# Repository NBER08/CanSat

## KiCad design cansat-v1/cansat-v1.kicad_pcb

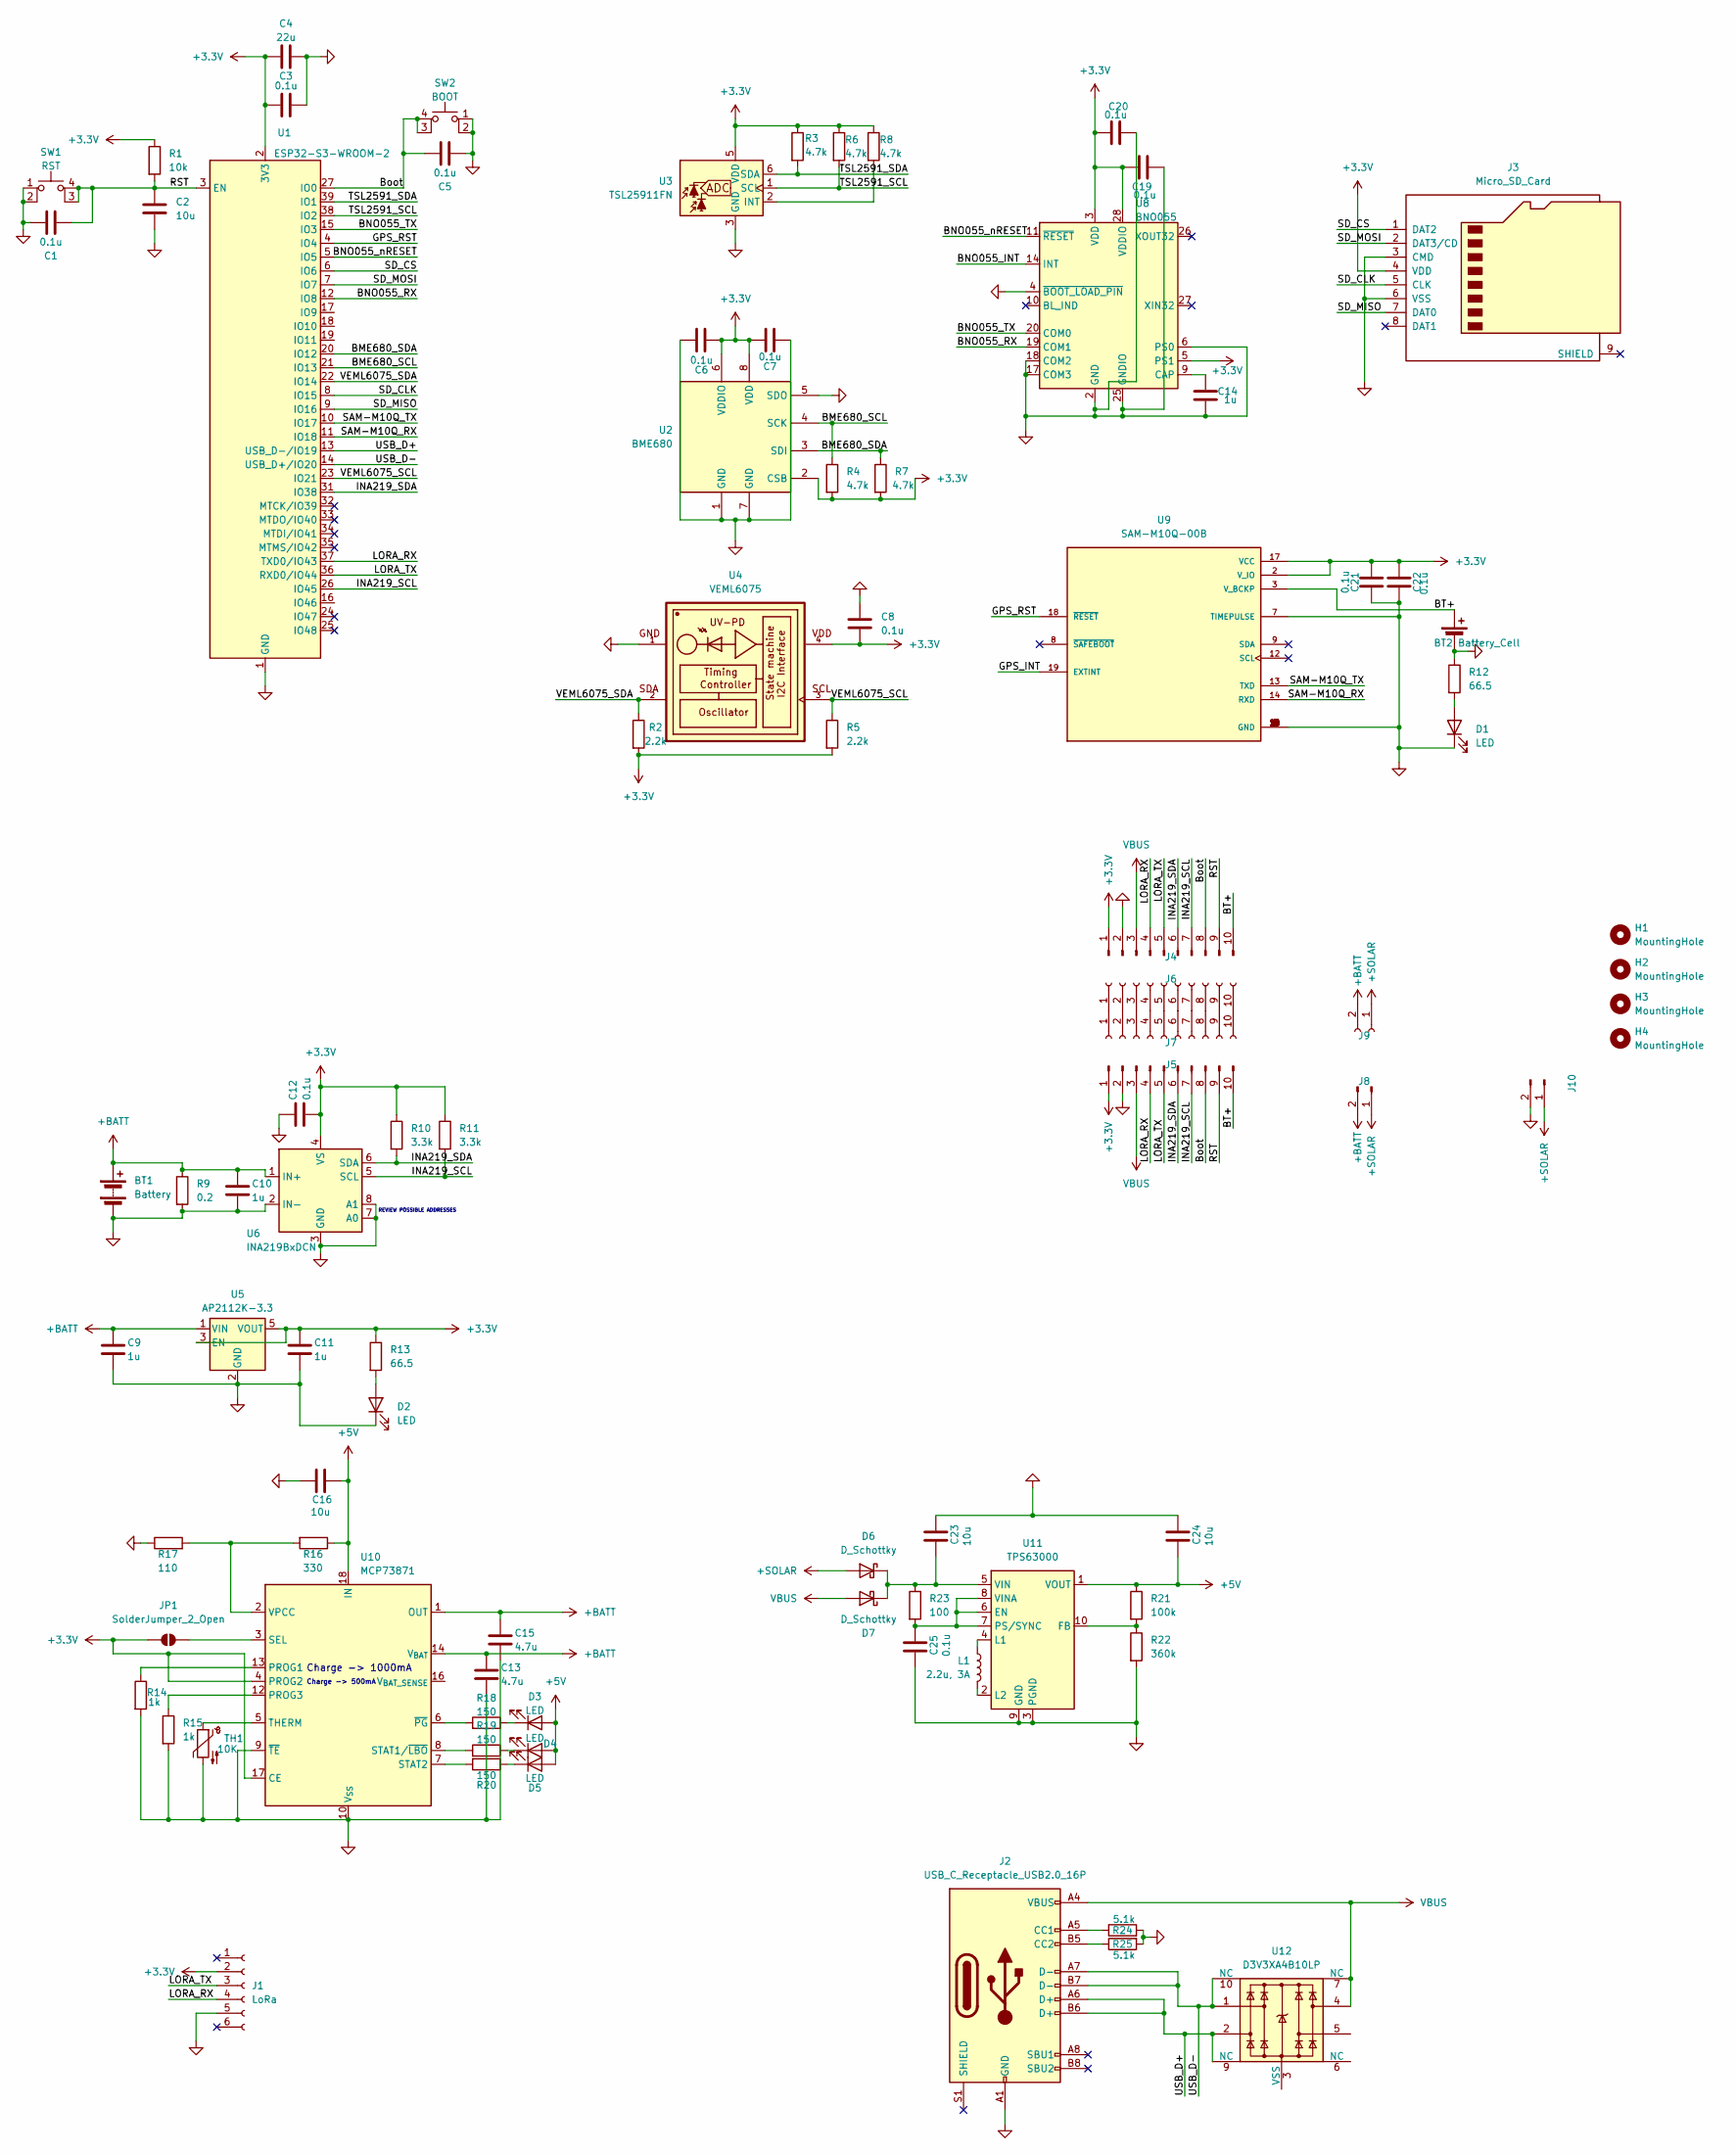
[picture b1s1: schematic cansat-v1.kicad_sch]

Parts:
BT1: Battery; AMASS_XT60-F_1x02_P7.20mm_Vertical
BT2: Battery_Cell; BatteryHolder_Keystone_3034_1x20mm
C1, C3, C5, C6, C7, C8, C12, C19, C20, C21, C22, C25: 0.1u; C_0603_1608Metric
C2, C16, C23, C24: 10u; C_0603_1608Metric
C4: 22u; C_0603_1608Metric
C9, C10, C11, C14: 1u; C_0603_1608Metric
C13, C15: 4.7u; C_0603_1608Metric
D1, D2, D3, D4, D5: LED; LED_1206_3216Metric_Pad1.42x1.75mm_HandSolder
D6, D7: D_Schottky; D_0603_1608Metric
H1, H2, H3, H4: MountingHole; MountingHole_3.2mm_M3
J1: LoRa; PinSocket_1x06_P2.54mm_Horizontal
J2: USB_C_Receptacle_USB2.0_16P; USB_C_Receptacle_G-Switch_GT-USB-7010ASV
J3: Micro_SD_Card; microSD_HC_Wuerth_693072010801
J4, J5: Conn_01x08_Pin; PinHeader_1x10_P2.54mm_Horizontal
J6, J7: Conn_01x08_Socket; PinSocket_1x10_P2.54mm_Vertical
J8: Conn_01x02_Pin; PinHeader_1x02_P2.54mm_Horizontal
J9: Conn_01x02_Socket; PinSocket_1x02_P2.54mm_Vertical
J10: Conn_01x02_Pin; JST_XH_B2B-XH-A_1x02_P2.50mm_Vertical
JP1: SolderJumper_2_Open; SolderJumper-2_P1.3mm_Open_TrianglePad1.0x1.5mm
L1: 2.2u, 3A; L_0603_1608Metric
R1: 10k; R_0603_1608Metric
R2, R5: 2.2k; R_0603_1608Metric
R3, R4, R6, R7, R8: 4.7k; R_0603_1608Metric
R9: 0.2; R_0603_1608Metric
R10, R11: 3.3k; R_0603_1608Metric
R12, R13: 66.5; R_1206_3216Metric
R14, R15: 1k; R_1206_3216Metric
R16: 330; R_1206_3216Metric
R17: 110; R_1206_3216Metric
R18, R19, R20: 150; R_1206_3216Metric
R21: 100k; R_1206_3216Metric
R22: 360k; R_1206_3216Metric
R23: 100; R_1206_3216Metric
R24, R25: 5.1k; R_1206_3216Metric
SW1: RST; SW_MEC_5GSH9
SW2: BOOT; SW_MEC_5GSH9
TH1: 10K; R_0603_1608Metric
U1: ESP32-S3-WROOM-2
U2: BME680; Bosch_LGA-8_3x3mm_P0.8mm_ClockwisePinNumbering
U3: TSL25911FN; AMS_TSL25911FN
U4: VEML6075; VISHAY_VEML6075_1.25X2X1
U5: AP2112K-3.3; SOT-23-5
U6: INA219BxDCN; SOT-23-8
U8: BNO055; LGA-28_5.2x3.8mm_P0.5mm
U9: SAM-M10Q-00B; XCVR_SAM-M10Q-00B; PARTREV R03
U10: MCP73871; QFN-20-1EP_4x4mm_P0.5mm_EP2.5x2.5mm
U11: TPS63000; Texas_DRC0010J_ThermalVias
U12: D3V3XA4B10LP; Diodes_UDFN-10_1.0x2.5mm_P0.5mm

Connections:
+3.3V: C3.1, C4.1, C6.1, C7.2, C8.2, C11.1, C12.2, C19.2, C20.2, C21.1, C22.1, J1.2, J3.4 (VDD), J4.1, J5.1, JP1.1 (A), R1.1, R2.2, R3.1, R4.2, R5.2, R6.1, R7.2, R8.1, R10.1, R11.1, R13.1, U1.2 (3V3), U2.2 (CSB), U2.6 (VDDIO), U2.8 (VDD), U3.5 (VDD), U4.4, U5.3 (EN), U5.5 (VOUT), U6.4 (VS), U8.3 (VDD), U8.5 (PS1), U8.28 (VDDIO), U9.2 (V_IO), U9.17 (VCC), U10.4 (PROG2), U10.17 (CE)
+5V: C16.1, C24.2, D3.2 (A), D4.2 (A), D5.2 (A), R16.1, R21.1, U10.18 (IN), U10.19 (IN), U11.1 (VOUT)
+BATT: BT1.1 (+), C9.1, C10.1, C13.1, C15.1, J8.2, J9.2, R9.1, U5.1 (VIN), U6.1 (IN+), U10.1 (OUT), U10.14 (V_{BAT}), U10.15 (V_{BAT}), U10.20 (OUT); also elsewhere on the board
+SOLAR: D6.2 (A), J8.1, J9.1, J10.1; also elsewhere on the board
/BME680_SCL: R4.1, U1.21 (IO13), U2.4 (SCK)
/BME680_SDA: R7.1, U1.20 (IO12), U2.3 (SDI)
/BNO055_INT: U8.14 (INT)
/BNO055_RX: U1.12 (IO8), U8.19 (COM1)
/BNO055_TX: U1.15 (IO3), U8.20 (COM0)
/BNO055_nRESET: U1.5 (IO5), U8.11 (~RESET)
/BT+: BT2.1 (+), J4.10, J5.10, U9.3 (V_BCKP)
/Boot: C5.2, J4.8, J5.8, SW2.3 (K), SW2.4 (A), U1.27 (IO0)
/GPS_INT: U9.19 (EXTINT)
/GPS_RST: U1.4 (IO4), U9.18 (~RESET)
/INA219_SCL: J4.7, J5.7, R11.2, U1.26 (IO45), U6.5 (SCL)
/INA219_SDA: J4.6, J5.6, R10.2, U1.31 (IO38), U6.6 (SDA)
/LORA_RX: J1.4, J4.4, J5.4, U1.37 (TXD0/IO43)
/LORA_TX: J1.3, J4.5, J5.5, U1.36 (RXD0/IO44)
/RST: C1.2, C2.1, J4.9, J5.9, R1.2, SW1.3 (K), SW1.4 (A), U1.3 (EN)
/SAM-M10Q_RX: U1.11 (IO18), U9.14 (RXD)
/SAM-M10Q_TX: U1.10 (IO17), U9.13 (TXD)
/SD_CLK: J3.5 (CLK), U1.8 (IO15)
/SD_CS: J3.1 (DAT2), U1.6 (IO6)
/SD_MISO: J3.7 (DAT0), U1.9 (IO16)
/SD_MOSI: J3.2 (DAT3/CD), U1.7 (IO7)
/TSL2591_SCL: R6.2, U1.38 (IO2), U3.1 (SCL)
/TSL2591_SDA: R3.2, U1.39 (IO1), U3.6 (SDA)
/USB_D+: J2.A6 (D+), J2.B6 (D+), U1.13 (USB_D-/IO19), U12.2, U12.9 (NC)
/USB_D-: J2.A7 (D-), J2.B7 (D-), U1.14 (USB_D+/IO20), U12.1, U12.10 (NC)
/VEML6075_SCL: R5.1, U1.23 (IO21), U4.3
/VEML6075_SDA: R2.1, U1.22 (IO14), U4.2
GND: BT1.2 (-), BT2.2 (-), C1.1, C2.2, C3.2, C4.2, C5.1, C6.2, C7.1, C8.1, C9.2, C10.2, C11.2, C12.1, C13.2, C14.2, C15.2, C16.2, C19.1, C20.1, C21.2, C22.2, C23.1, C24.1, C25.2, D1.1 (K), D2.1 (K), J1.5, J2.A1 (GND), J2.A12 (GND), J2.B1 (GND), J2.B12 (GND), J3.3 (CMD), J3.6 (VSS), J4.2, J5.2, J10.2, R9.2, R12.1, R14.2, R15.2, R17.1, R22.2, R24.2, R25.2, SW1.1, SW1.2, SW2.1, SW2.2, TH1.2, U1.1 (GND), U1.40 (GND), U1.41 (GND), U2.1 (GND), U2.5 (SDO), U2.7 (GND), U3.3 (GND), U4.1, U5.2 (GND), U6.2 (IN-), U6.3 (GND), U6.7 (A0), U6.8 (A1), U8.2 (GND), U8.4 (~BOOT_LOAD_PIN), U8.6 (PS0), U8.17 (COM3), U8.18 (COM2), U8.25 (GNDIO), U9.1 (GND), U9.4 (GND), U9.5 (GND), U9.6 (GND), U9.7 (TIMEPULSE), U9.10 (GND), U9.11 (GND), U9.15 (GND), U9.16 (GND), U9.20 (GND), U10.9 (~TE), U10.10 (V_{SS}), U10.11 (V_{SS}), U10.21 (V_{SS}), U11.3 (PGND), U11.9 (GND), U11.11 (PGND)
unnamed: D1.2 (A), R12.2
unnamed: D2.2 (A), R13.2
unnamed: D3.1 (K), R18.1
unnamed: D4.1 (K), R19.1
unnamed: D5.1 (K), R20.1
unnamed: C23.2, D6.1 (K), D7.1 (K), R23.1, U11.5 (VIN)
unnamed: J2.A5 (CC1), R24.1
unnamed: J2.B5 (CC2), R25.1
unnamed: J6.1, J7.1
unnamed: J6.2, J7.2
unnamed: J6.3, J7.3
unnamed: J6.4, J7.4
unnamed: J6.5, J7.5
unnamed: J6.6, J7.6
unnamed: J6.7, J7.7
unnamed: J6.8, J7.8
unnamed: J6.9, J7.9
unnamed: J6.10, J7.10
unnamed: JP1.2 (B), U10.3 (SEL)
unnamed: R8.2, U3.2 (INT)
unnamed: C14.1, U8.9 (CAP)
unnamed: R14.1, U10.13 (PROG1)
unnamed: R15.1, U10.12 (PROG3)
unnamed: R19.2, U10.8 (STAT1/~LBO)
unnamed: R20.2, U10.7 (STAT2)
unnamed: TH1.1, U10.5 (THERM)
unnamed: R16.2, R17.2, U10.2 (VPCC)
unnamed: R18.2, U10.6 (~PG)
unnamed: C25.1, R23.2, U11.6 (EN), U11.7 (PS/SYNC), U11.8 (VINA)
unnamed: R21.2, R22.1, U11.10 (FB)
unnamed: L1.1, U11.4 (L1)
unnamed: L1.2, U11.2 (L2)
unnamed: U12.3 (VSS), U12.8 (VSS)
VBUS: D7.2 (A), J2.A4 (VBUS), J2.A9 (VBUS), J2.B4 (VBUS), J2.B9 (VBUS), J4.3, J5.3, U12.4, U12.7 (NC)

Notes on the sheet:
Charge -> 1000mA
Charge -> 500mA
REVIEW POSSIBLE ADDRESSES

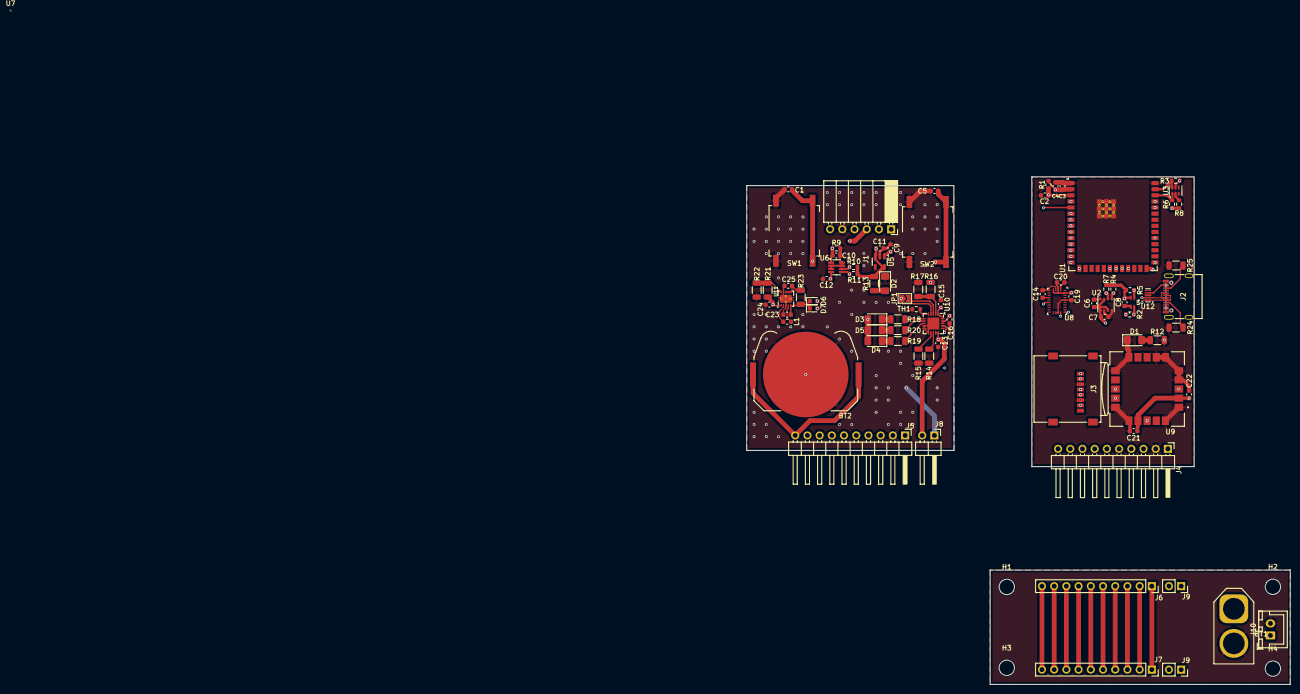
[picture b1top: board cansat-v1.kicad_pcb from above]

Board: 4 copper layers, 113.1 x 105.6 mm, 89 parts (0 on the bottom side), 64 nets.

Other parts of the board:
J9#2: Conn_01x02_Socket; PinSocket_1x02_P2.54mm_Vertical
U7: via_4-2

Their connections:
+BATT: J9#2.2; also elsewhere on the board
+SOLAR: J9#2.1; also elsewhere on the board

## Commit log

2025-05-23 Create test
2025-05-27 Added PDR.tex
2025-05-28 Added the pcb file folder for v1
2025-05-28 Added radio_test1.tex
2025-05-28 Added fogyasztas
